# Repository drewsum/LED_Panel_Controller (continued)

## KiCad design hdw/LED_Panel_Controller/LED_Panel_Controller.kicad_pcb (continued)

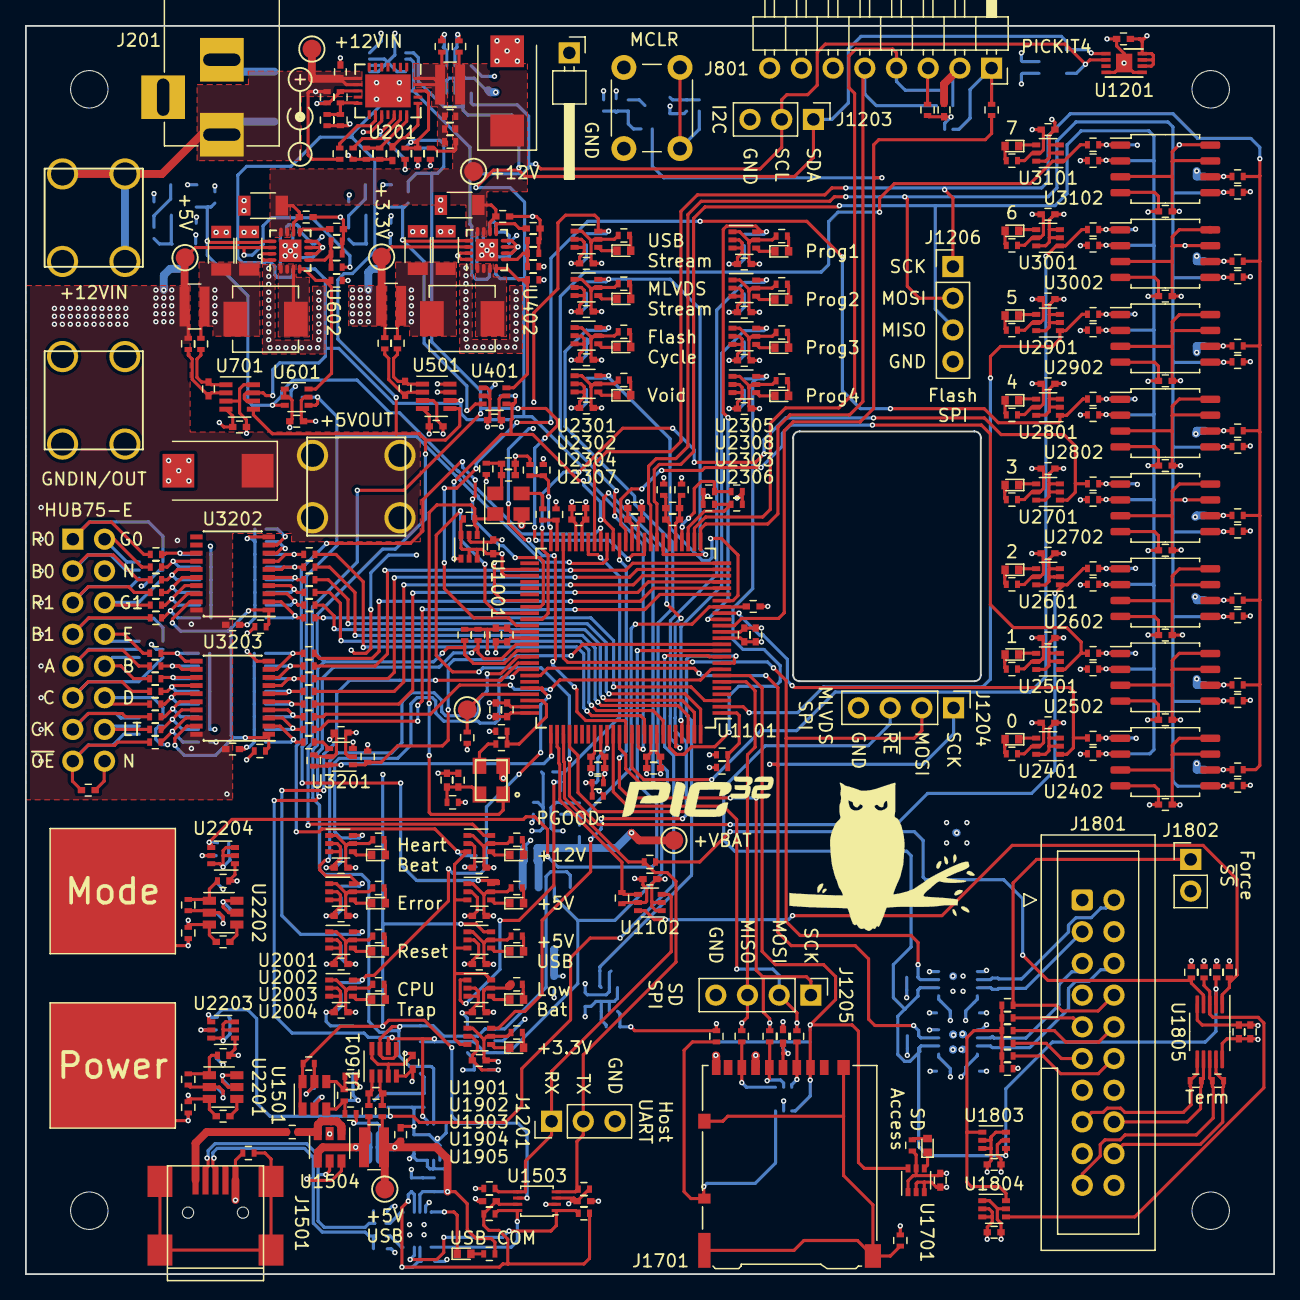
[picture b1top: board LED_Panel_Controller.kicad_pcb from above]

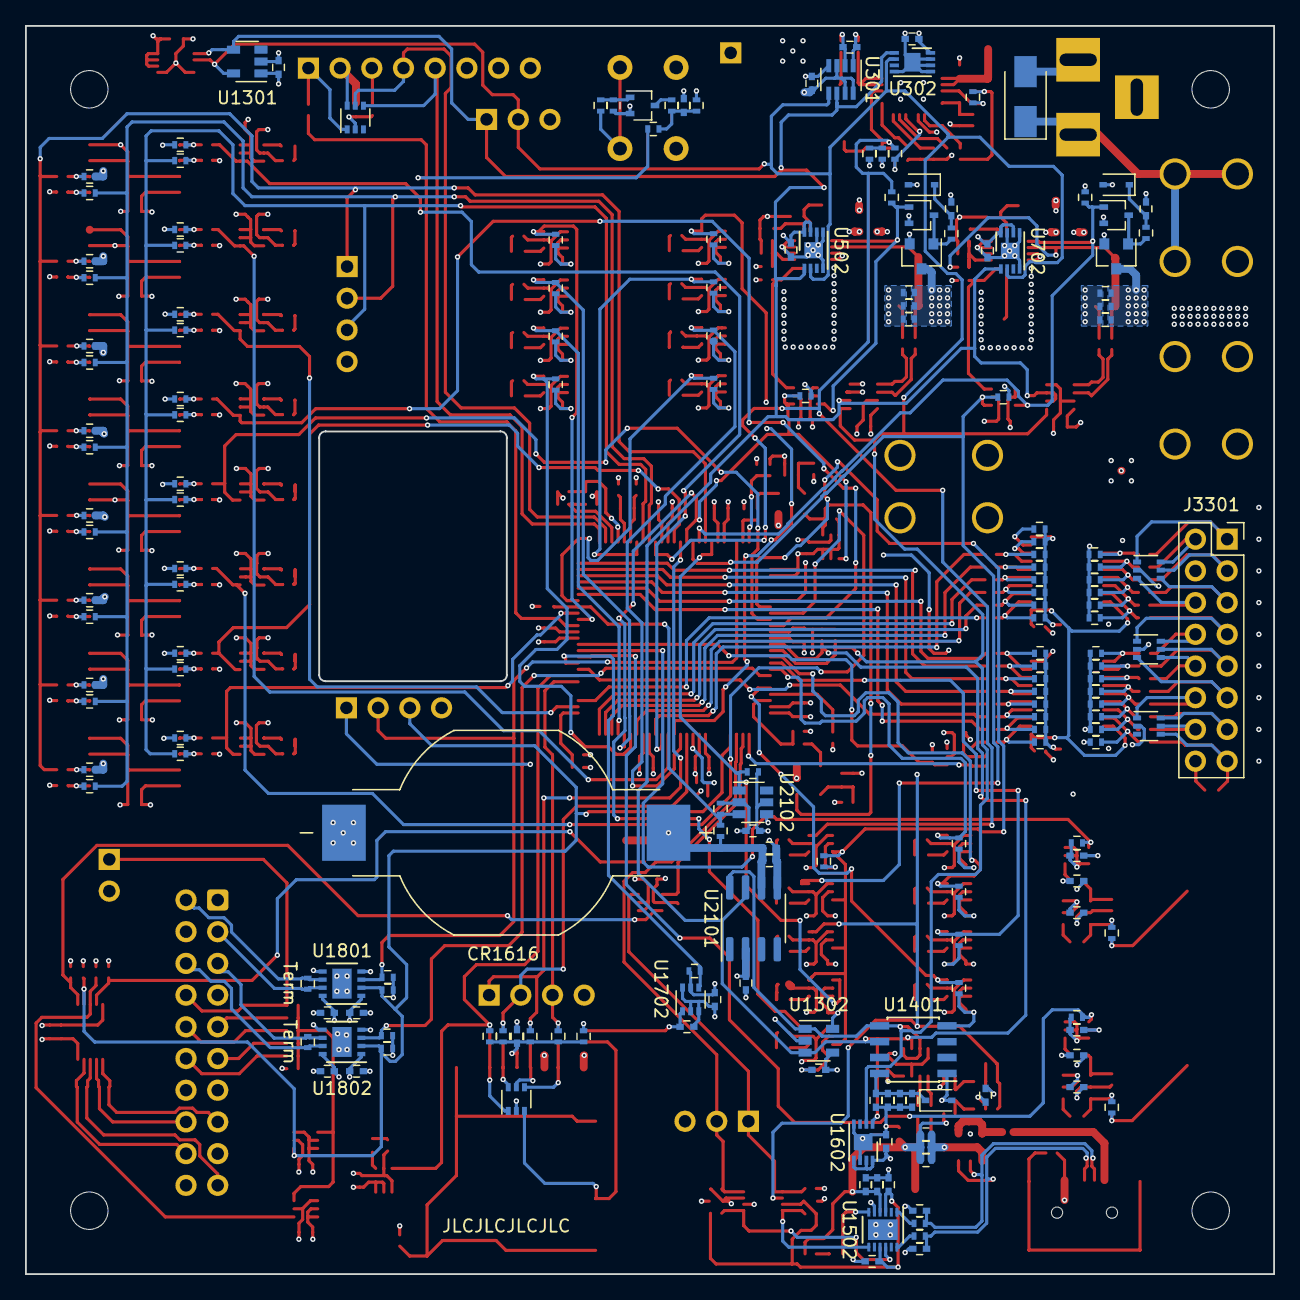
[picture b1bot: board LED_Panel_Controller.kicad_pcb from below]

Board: 4 copper layers, 100.0 x 100.0 mm, 589 parts (189 on the bottom side), 305 nets.

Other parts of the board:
C1503: 10uF; C_0402
C1504: 0.1uF; C_0402
R1505, R1506, R1508, R1509: 100k; R_0402
R1510, R1517: 10; R_0402
R1511: 0.02; R_0612
R1512, R1513, R1514: 0; R_0402
TP1501: TP; Test_Point
symbol1: Owl_1_Logo
symbol2: PIC32_Logo

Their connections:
+3.3V_USB: R1508.1, R1509.1; also elsewhere on the board
PIC32MZ_UART_RX_BUF: R1508.2; also elsewhere on the board
PIC32MZ_UART_TX_BUF: R1509.2; also elsewhere on the board
POS5_USB_SNS+: R1517.1; also elsewhere on the board
POS5_USB_SNS-: R1510.1; also elsewhere on the board

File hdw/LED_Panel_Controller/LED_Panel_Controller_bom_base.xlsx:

Component | References | Value | Quantity Per PCB | Digi-Key PN | Configuration
1 | BT2101 | CR1616 | 1 | P034-ND | BACKUP_RTC
2 | BT2102 | CR1616_Holder | 1 | BU1632SM-JJ-GCT-ND | BACKUP_RTC
3 | C3301 | 15pF | 1 | 587-1949-1-ND | DNP
4 | C1509 C1510 | 47pF | 2 | 311-3783-1-ND | USB
5 | C201 C404 C604 | 10nF | 3 | 399-3066-1-ND
6 | C2201 C2202 | 10nF | 2 | 399-3066-1-ND | PUSH
7 | C202 C401 C405 C601 C605 C801 C802 C901 C902 C905 C907 C909 C910 C913 C915 C100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 | 0.1uF | 43 | 490-10698-1-ND
8 | C301 C302 C303 C501 C502 C503 C701 C702 C703 C1201 C1601 C1602 C1603 | 0.1uF | 13 | 490-10698-1-ND | Telemetry
9 | C1301 | 0.1uF | 1 | 490-10698-1-ND | DNP
10 | C1404 | 0.1uF | 1 | 490-10698-1-ND | ETC
11 | C1501 C1502 C1504 C1506 C1507 | 0.1uF | 5 | 490-10698-1-ND | USB
12 | C1701 C1703 C1705 | 0.1uF | 3 | 490-10698-1-ND | SD
13 | C1801 C1803 C1804 C2302 | 0.1uF | 4 | 490-10698-1-ND | Multidrop
14 | C2101 C2103 C2104 C2105 | 0.1uF | 4 | 490-10698-1-ND | BACKUP_RTC
15 | C2203 C2204 C2207 C2208 | 0.1uF | 4 | 490-10698-1-ND | PUSH
16 | C2401 C2402 C2501 C2502 C2601 C2602 C2701 C2702 C2801 C2802 C2901 C2902 C3001 C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 | 0.1uF | 16 | 490-10698-1-ND | SPI_FLASH
17 | C403 C603 C903 C904 C906 C908 C911 C912 C914 C916 C1004 C1005 C1807 C1808 | 10uF | 14 | 1276-1451-1-ND
18 | C1401 C1402 C1403 | 10uF | 3 | 1276-1451-1-ND | ETC
19 | C1503 | 10uF | 1 | 1276-1451-1-ND | USB
20 | C1702 C1704 | 10uF | 2 | 1276-1451-1-ND | SD
21 | C1802 | 10uF | 1 | 1276-1451-1-ND | Multidrop
22 | C2102 | 10uF | 1 | 1276-1451-1-ND | BACKUP_RTC
23 | C2205 C2206 | 10uF | 2 | 1276-1451-1-ND | PUSH
24 | C402 C406 C407 C602 C606 C607 | 10uF | 6 | 399-8153-1-ND
25 | C203 C3302 | 100uF | 2 | 718-1102-1-ND
26 | D201 | 24V | 1 | SMAJ24CALFCT-ND | DNP
27 | D1401 | BAT48JFILM | 1 | 497-5711-1-ND | ETC
28 | D401 D601 | BAT48JFILM | 2 | 497-5711-1-ND
29 | D1701 | Green | 1 | 1497-1219-1-ND | SD
30 | D1901 D1902 D1903 D1905 D2001 D2301 D2303 D2304 D2305 D2306 D2307 D2308 | Green | 12 | 1497-1219-1-ND
31 | D2302 | Green | 1 | 1497-1219-1-ND | Multidrop
32 | D2401 D2501 D2601 D2701 D2801 D2901 D3001 D3101 | Green | 8 | 1497-1219-1-ND | SPI_FLASH
33 | D1904 D2002 D2003 D2004 | Red | 4 | 1497-1174-1-ND
34 | D1702 | SP0505BAJT | 1 | F3160CT-ND | SD
35 | D801 D3301 D3302 D3303 | SP0505BAJT | 4 | F3160CT-ND
36 | D1501 | Yellow | 1 | 1497-1198-1-ND | USB
50 | J1802 | Force SS | 1 |  | NONE
51 | J202 J203 | Keystone_8191 | 2 | 36-8191-ND | DNP
52 | J3302 | Keystone_8191 | 1 | 36-8191-ND
53 | J1701 | Micro_SD_Card_Det_Hirose_DM3AT | 1 | HR1964CT-ND | SD
54 | J1801 | Multidrop Expansion | 1 | 732-2096-ND | Multidrop
55 | J801 | PICKIT4 | 1 |  | DEV
56 | J1201 J1203 | PIC_UART | 2 |  | DNP
57 | J3301 | Panel Data | 1 | S9196-ND
58 | J1501 | USB_B_Mini | 1 | 732-2109-1-ND | USB
59 | J1204 J1205 J1206 | WIFI_SPI | 3 |  | DNP
60 | L401 L601 | 2.2uH | 2 | 541-1236-1-ND
61 | L801 L802 L901 L902 L1001 L1002 | 600R 0.5A | 6 | 490-5441-1-ND
62 | L1501 L1502 | 600R 0.5A | 2 | 490-5441-1-ND | USB
63 | L1701 | 600R 0.5A | 1 | 490-5441-1-ND | SD
64 | MK3403 MK3404 MK3407 MK3408 | Screw | 4 | 36-9900-ND | DEV
65 | MK3401 MK3402 MK3405 MK3406 | Standoff | 4 | 1772-1220-ND | DEV
66 | Q401 Q601 Q801 | BSS214NW | 3 | BSS214NWH6327XTSA1CT-ND
67 | Q402 Q602 | ZXMS6004FFTA | 2 | ZXMS6004FFCT-ND
68 | R1104 | 0 | 1 | RMCF0402ZT0R00CT-ND | Multidrop
69 | R209 R210 R211 R408 R409 R410 R608 R609 R610 R1512 R1513 R1514 | 0 | 12 | RMCF0402ZT0R00CT-ND | ~Telemetry
70 | R1813 | 0 | 1 | RMCF0402ZT0R00CT-N | MODULE0
71 | R1814 | 0 | 1 | RMCF0402ZT0R00CT-N | MODULE1
72 | R1815 | 0 | 1 | RMCF0402ZT0R00CT-N | MODULE2
73 | R1816 | 0 | 1 | RMCF0402ZT0R00CT-N | MODULE3
74 | R1817 | 0 | 1 | RMCF0402ZT0R00CT-N | MODULE4
75 | R402 R405 R605 | 0 | 3 | RMCF0402ZT0R00CT-ND
76 | R208 R407 R607 R1511 | 0.02 | 4 | P16010CT-ND | Telemetry
77 | R801 R803 R1003 R1004 R1702 R1709 R1710 R1711 R2409 R2509 R2609 R2709 R2809 R29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 | 10 | 44 | RMCF0402FT10R0CT-ND
78 | R207 R213 R406 R411 R606 R611 R1202 R1510 R1517 | 10 | 9 | RMCF0402FT10R0CT-ND | Telemetry
79 | R1204 R2402 R2403 R2404 R2502 R2503 R2504 R2602 R2603 R2604 R2702 R2703 R2704 R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 | 10 | 25 | RMCF0402FT10R0CT-ND | SPI_FLASH
80 | R1206 | 10 | 1 | RMCF0402FT10R0CT-ND | ETC
81 | R1208 | 10 | 1 | RMCF0402FT10R0CT-ND | Multidrop
82 | R1210 | 10 | 1 | RMCF0402FT10R0CT-ND | BACKUP_RTC
83 | R1515 R1516 | 27 | 2 | RMCF0402FT27R0CT-ND | USB
84 | R1809 R1810 R1811 R1812 | 120 | 4 | RMCF0402FT120RCT-ND | Term
85 | R1501 | 1k | 1 | RMCF0402FT1K00CT-ND | USB
86 | R1701 | 1k | 1 | RMCF0402FT1K00CT-ND | SD
87 | R204 R215 R216 R217 R805 R1902 R1903 R1904 R1905 R1906 R2003 R2004 R2007 R2008 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 | 1k | 21 | RMCF0402FT1K00CT-ND
88 | R2201 R2202 R2203 R2204 | 1k | 4 | RMCF0402FT1K00CT-ND | PUSH
89 | R2305 | 1k | 1 | RMCF0402FT1K00CT-ND | Multidrop
90 | R2401 R2501 R2601 R2701 R2801 R2901 R3001 R3101 | 1k | 8 | RMCF0402FT1K00CT-ND | SPI_FLASH
91 | R1503 | 6.04k | 1 | RMCF0402FT6K04CT-ND | USB
92 | R202 R205 R206 R212 R218 R219 R220 R221 R401 R403 R404 R601 R602 R603 R604 R802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 | 10k | 102 | RMCF0402FT10K0CT-ND
93 | R1507 | 10k | 1 | RMCF0402FT10K0CT-ND | USB
94 | R214 | 10k | 1 | RMCF0402FT10K0CT-ND | DNP
95 | R2205 R2206 R2207 R2208 | 10k | 4 | RMCF0402FT10K0CT-ND | PUSH
96 | R2405 R2406 R2407 R2505 R2506 R2507 R2605 R2606 R2607 R2705 R2706 R2707 R2805 R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 | 10k | 24 | RMCF0402FT10K0CT-ND | SPI_FLASH
97 | R1504 | 40.2k | 1 | RMCF0402FT40K2CT-ND | USB
98 | R201 R203 R1505 R1506 R1508 R1509 | 100k | 6 | RMCF0402FT100KCT-ND
99 | R413 R613 | 180k | 2 | RMCF0402FT180KCT-ND | DNP
100 | R2102 | 220k | 1 | RMCF0402FT220KCT-ND | BACKUP_RTC
101 | R1502 | 487k | 1 | RMCF0402FT487KCT-ND | USB
102 | R412 | 562k | 1 | RMCF0402FT562KCT-ND | DNP
103 | R612 | 953k | 1 | RMCF0402FT953KCT-ND | DNP
104 | R2101 | 1.07M | 1 | RMCF0402FT1M07CT-ND | BACKUP_RTC
106 | SW801 | MRST | 1
107 | U3202 U3203 | 74HCT541 | 2 | 296-26499-1-ND
108 | U1001 | 74LVC1G97 | 1 | 1727-1772-1-ND
109 | U401 U601 U1102 | 74LVC1G97 | 3 | 1727-1772-1-ND
110 | U1701 | 74LVC1G97 | 1 | 1727-1772-1-ND | SD
111 | U1702 | 74LVC1G97 | 1 | 1727-1772-1-ND | SD
112 | U1803 | 74LVC1G97 | 1 | 1727-1772-1-ND | Multidrop
113 | U1804 U2302 | 74LVC1G97 | 2 | 1727-1772-1-ND | Multidrop
114 | U1901 U1902 U1903 U1905 | 74LVC1G97 | 4 | 1727-1772-1-ND
115 | U1904 | 74LVC1G97 | 1 | 1727-1772-1-ND
116 | U2001 U2002 U2003 U2004 U2301 U2303 U2304 U2305 U2306 U2307 U2308 | 74LVC1G97 | 11 | 1727-1772-1-ND
117 | U2203 U2204 | 74LVC1G97 | 2 | 1727-1772-1-ND | PUSH
118 | U2401 U2501 U2601 U2701 U2801 U2901 U3001 U3101 | 74LVC1G97 | 8 | 1727-1772-1-ND | SPI_FLASH
119 | U3201 | 74LVC1G97 | 1 | 1727-1772-1-ND
120 | U1302 | AT24CS32-STUM | 1 | AT24CS32-STUM-T
121 | U2201 U2202 | AT42QT1010-TSHR | 2 | AT42QT1010-TSHRCT-ND | PUSH
122 | U1401 | DS1683 | 1 | DS1683S+-ND | ETC
123 | U2101 | DS3231MZ | 1 | DS3231MZ+-ND | BACKUP_RTC
124 | U1502 | FT234XD | 1 | 768-1178-1-ND | USB
125 | U301 U501 U701 U1601 | INA219BxDCN | 4 | 296-46420-1-ND | Telemetry
126 | U1301 | LTC1694 | 1 | LTC1694CS5#TRPBFCT-ND | DNP
127 | U302 U502 U702 U1201 U1602 | MCP9804 | 5 | MCP9804T-E/MCCT-ND | Telemetry
128 | U1101 | PIC32MZ2048EFG100_IPF | 1 | PIC32MZ2048EFG100-I/PF-ND
129 | U1801 U1802 | SN65MLVD3 | 2 | 296-21314-1-ND | Multidrop
130 | U2402 U2502 U2602 U2702 U2802 U2902 U3002 U3102 | SST25VF080B | 8 | SST25VF080B-50-4I-S2AE-T | SPI_FLASH
131 | U1805 | THVD1552 | 1 | 296-51654-1-ND | Multidrop
132 | U1501 | TLV6700 | 1 | 296-51696-1-ND | USB
133 | U2102 | TLV6700 | 1 | 296-51696-1-ND | BACKUP_RTC
134 | U1504 | TPD3S014DBVR | 1 | 296-38835-1-ND | USB
135 | U201 | TPS26600RHFT | 1 | 296-45478-1-ND
136 | U402 | TPS62132 | 1 | 296-29936-1-ND
137 | U602 | TPS62133 | 1 | 296-30225-1-ND
138 | U1503 | TXB0102DCU | 1 | 296-22862-1-ND
139 | X1001 | ASE-8.000MHz | 1 | 535-9558-1-ND
140 | X1002 | ECS-327KE | 1 | XC1751CT-ND
Component Groups:
Component Count:
Fitted Components:
Number of PCBs:
Total components:
Schematic Version:
Schematic Date:
PCB Variant:
BoM Date:
Schematic Source:
KiCad Version:

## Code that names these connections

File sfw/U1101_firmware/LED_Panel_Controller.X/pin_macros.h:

#ifndef _PIN_MACROS_H    /* Guard against multiple inclusion */
#define _PIN_MACROS_H

#include <xc.h>

#define HIGH    1
#define LOW     0

// These pin macros allow for easier manipulation of GPIO with matching
// signal names from the hardware schematic

// Port A
#define nFLASH_SPI_CE0_PIN              LATAbits.LATA0
#define nFLASH_SPI_CE1_PIN              LATAbits.LATA1
#define nFLASH_SPI_CE2_PIN              LATAbits.LATA2
#define nFLASH_SPI_CE3_PIN              LATAbits.LATA3
#define nFLASH_SPI_CE4_PIN              LATAbits.LATA4
#define nFLASH_SPI_CE5_PIN              LATAbits.LATA5
#define nFLASH_SPI_CE6_PIN              LATAbits.LATA6
#define nFLASH_SPI_CE7_PIN              LATAbits.LATA7
#define nETC_CONFIG_PIN                 PORTAbits.RA9
#define nMLVDS_CONFIG_PIN               PORTAbits.RA10
#define ERROR_LED_PIN                   LATAbits.LATA14
#define RESET_LED_PIN                   LATAbits.LATA15

// Port B
#define ROW_A_PIN                       LATBbits.LATB0
#define ROW_B_PIN                       LATBbits.LATB1
#define ROW_C_PIN                       LATBbits.LATB2
#define ROW_D_PIN                       LATBbits.LATB3
#define ROW_E_PIN                       LATBbits.LATB4
#define PANEL_LAT_PIN                   LATBbits.LATB5
#define MLVDS_STREAM_MODE_LED_PIN       LATBbits.LATB8
#define POS12_PGOOD_PIN                 PORTBbits.RB11
#define POS5_PGOOD_PIN                  PORTBbits.RB12
#define POS5_RUN_PIN                    LATBbits.LATB13
#define VBAT_PGOOD_PIN                  PORTBbits.RB15

// Port C
#define nSD_SPI_CS_PIN                  LATCbits.LATC2
#define nSD_CARD_DET_PIN                PORTCbits.RC4
#define nBACKUP_RTC_CONFIG_PIN          PORTCbits.RC15

// Port D
#define CPU_TRAP_LED_PIN                LATDbits.LATD0
#define nPANEL_OE_PIN                   LATDbits.LATD1
#define HEARTBEAT_LED_PIN               LATDbits.LATD9

// Port E
#define VOID_MODE_LED_PIN               PORTEbits.RE9

// Port F
#define nTELEMETRY_CONFIG_PIN           PORTFbits.RF0
#define POS5_USB_PGOOD_PIN              PORTFbits.RF2
#define PGOOD_LED_SHDN_PIN              LATFbits.LATF8
#define POS3P3_PGOOD_PIN                PORTFbits.RF12

// Port G
#define USB_STREAM_MODE_LED_PIN         LATGbits.LATG0
#define FLASH_SLIDESHOW_MODE_LED_PIN    LATGbits.LATG1
#define PROG1_MODE_LED_PIN              LATGbits.LATG9
#define PROG2_MODE_LED_PIN              LATGbits.LATG12
#define PROG3_MODE_LED_PIN              LATGbits.LATG13
#define PROG4_MODE_LED_PIN              LATGbits.LATG14
#define nSPI_FLASH_CONFIG_PIN           PORTGbits.RG15

#endif /* _PIN_MACROS_H */

/* *****************************************************************************
 End of File
 */

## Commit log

2020-08-25 git ignoring
2020-08-25 Added block brainstorming block diagram
2020-09-09 Started schematic
2020-09-09 Added todo list item
2020-09-20 Many sch updates
2020-09-20 log's first
2020-10-04 reworked some USB stuff
2020-10-06 USB bridge sheet work
2020-12-24 lots of schematic progress
2021-02-01 made a lot more schematic progress
2021-02-01 fixed level shifter sheet
2021-02-01 lots of MCU pin assignments
2021-02-02 more schematic progress
2021-02-03 assigned a lot of nets to MCU pins
2021-02-07 added some test points, ambient temp sensor
2021-03-24 Added panel dimming OR gate
2021-03-25 more schematic development
2021-03-31 added digikey pns, footprints, bom scrubbed
2021-03-31 assigned I2C addresses
2021-03-31 ran erc, annotated schematic, added hardstraps to MCU
2021-04-01 reviewed schematic
2021-04-01 generated first pass netlist
2021-04-01 imported netlist to PCB
2021-04-01 design rules, hide passive refdes
2021-04-01 separated function groups on PCB
2021-04-01 some SPI Flash placement
2021-04-01 more serial flash layout
2021-04-02 fixed SPI flash pull resistors, more PCB placement
2021-04-09 more PCB grouping, fanout optimization
2021-04-09 more PCB grouping
2021-04-14 USB/power PCB grouping
2021-04-14 LED PCB grouping
2021-04-14 finished pcb grouping by sheet
2021-04-15 established board outline for connector cutout
2021-04-15 optimized panel signal level shifter signal locations
2021-04-15 arranging major PCB functional blocks
2021-04-15 more major PCB functional blocks
2021-04-15 PCB function blocks taking shape
2021-04-16 refined power cable hole cutout location
2021-04-16 finished arranging functional blocks on PCB
2021-05-05 started routing PCB
2021-05-07 much more PCB layout
2021-05-08 much more PCH progress, added SW node guard rings
2021-05-13 restructured SPI FLASH layout/placement
2021-05-13 starting to route sensitive signal nets
2021-05-13 more sensitive routes
2021-05-22 more manual routing
2021-05-29 having a mid-project crisis
2021-05-30 reworked schematic to use MLVDS connector instead of wifi module
2021-05-30 pulled MLVDS port into PCB
2021-05-31 started PCB grouping for multidrop expansion port
2021-06-04 arranged more parts on PCB
2021-06-05 completed more routing, pre autorouter
2021-06-05 routded diff pairs, other critical nets
2021-06-05 going into autorouter
2021-06-05 ran autorouter
2021-06-05 got unroutes to 0
2021-06-05 lots of autoroute cleanups
2021-06-05 more cleanup
2021-06-08 lots of cleanup, DRC
2021-06-08 added some more digikey part numbers to schematic
2021-06-09 added BOMs, some consolidation
2021-06-11 final hardware commit
2021-06-11 updated block diagram
2021-06-12 regenerated PDF
2021-06-12 removed unneeded schematic file
2021-06-12 created panel control board firmware
2021-06-12 added lots of core firmware modules
2021-06-12 added pin macros
2021-06-17 added gpio setup code
2021-06-17 added PPS pin map assignment code
2021-07-15 fixed POSC clocking setup issue
2021-07-15 got heartbeat working
2021-07-16 got USB UART working, corrected clocking
2021-07-16 added main.h, USB UART bridge flash image
2021-07-16 added cause of reset, prefetch
2021-07-16 heartbeat services, trimmed some serial command fat
2021-07-16 added I2C master code, switched to optimization level 1
2021-07-19 copied over I2C telemetry code
2021-07-19 added ADC code
2021-07-19 ported elapsed time counter
2021-07-20 got rtcc and backup rtcc working
2021-07-20 added cap touch pushbutton code
2021-07-20 added basic code to enable/disable +5V power supply
2021-07-22 added PMP code
2021-07-22 added some PMP DMA code, untested
2021-07-22 added more untested panel drive code
2021-07-22 added multiplexing on-time timer code, still all untested
2021-07-23 got some data showing up on panel
2021-07-24 got panel multiplexing working properly with PMP and DMA
2021-07-27 corrected PMP DMA source register selection, added random image code
2021-08-01 added beginning of python image conversion script
2021-08-05 got image conversion script working
2021-08-05 added gamma correction code in conversion script
2021-08-05 gamma correction bug fixes
2021-08-06 fixed telemetry bug that would bog down CPU while multiplexing is enabled
2021-08-06 added code to turn LE Ddisplay on and off with power button press
2021-08-06 optimized PMP bus timing
2021-08-06 got panel dimming working
2021-08-11 added MCU periheral map spreadsheet, more USB data transfer code
2021-08-11 got basic python serial data flow working
2021-08-12 got python USB image transfers working
2021-08-12 some python script enhancements
2021-08-12 fixed MCU firmware bug that causes received serial images to get corrupted
2021-08-13 added support for I2C EEPROM
2021-08-14 got basic SPI Flash code working
2021-08-15 making progress on flash storage
2021-08-15 got SPI Flash storage working
2021-08-15 got image slot abstraction working for spi flash
2021-08-15 many NVM image storage optimizations
2021-08-18 added lots of external image storage management code
2021-08-21 got slot tracking working
2022-06-19 added basic code for external spi flash slideshows
2022-07-04 refactored some data management code
2022-07-04 more image mngmt refactoring
2022-07-04 implemented void mode
2022-07-04 added mode leds
2022-07-04 added DMA transfer for coping scratchpad to buffer
2022-07-04 fixed scratchpad DMA bug
2022-07-04 void_mode_updates
2022-12-10 more firmware and script stuff!
2022-12-10 made power button actually do something
2022-12-10 got mode button working
2022-12-10 added usb command to manually set mode
2022-12-10 removed unused code for unused serial command
2022-12-10 added usb stream example script
2022-12-10 added script to stream spotify artwork over serial
2022-12-10 spotify stream bugfixes
2022-12-10 updated pip requirements
2022-12-10 spotify script bug fixes
